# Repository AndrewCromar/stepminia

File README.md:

# Stepminia

Desktop finger stepmania dance-pad.

Assebly instructions [here](ASSEMBLY.md).

## PCB

Made in Kicad. Find the production files in the pcb folder to have it manufacured (JLCPCB).

You may notice the simple and integrated pcbs. This is because I wanted to learn how to integrate a microcontroller (rp2040) into my pcb design.. but when I went to have it made it was gonna cost $100! Its not that much but I have other things I wanna buy right now. So I made the simple version that just has holes for a Waveshare Zero to be soldered on.

## Firmware

The firmware is in the firmware folder and there will likly be a compiled version of it also in that folder.

> Wow really I had no clue the firmware would be in that folder bro.

## CAD

Right now I'm making the cad stuff in OnShape so I dont have files for it. I'll download the stls and put them in the cad folder when I'm done with them.

> I also my link to the OnShape files and/or download the files as solidworks parts if I can so people can make changes.

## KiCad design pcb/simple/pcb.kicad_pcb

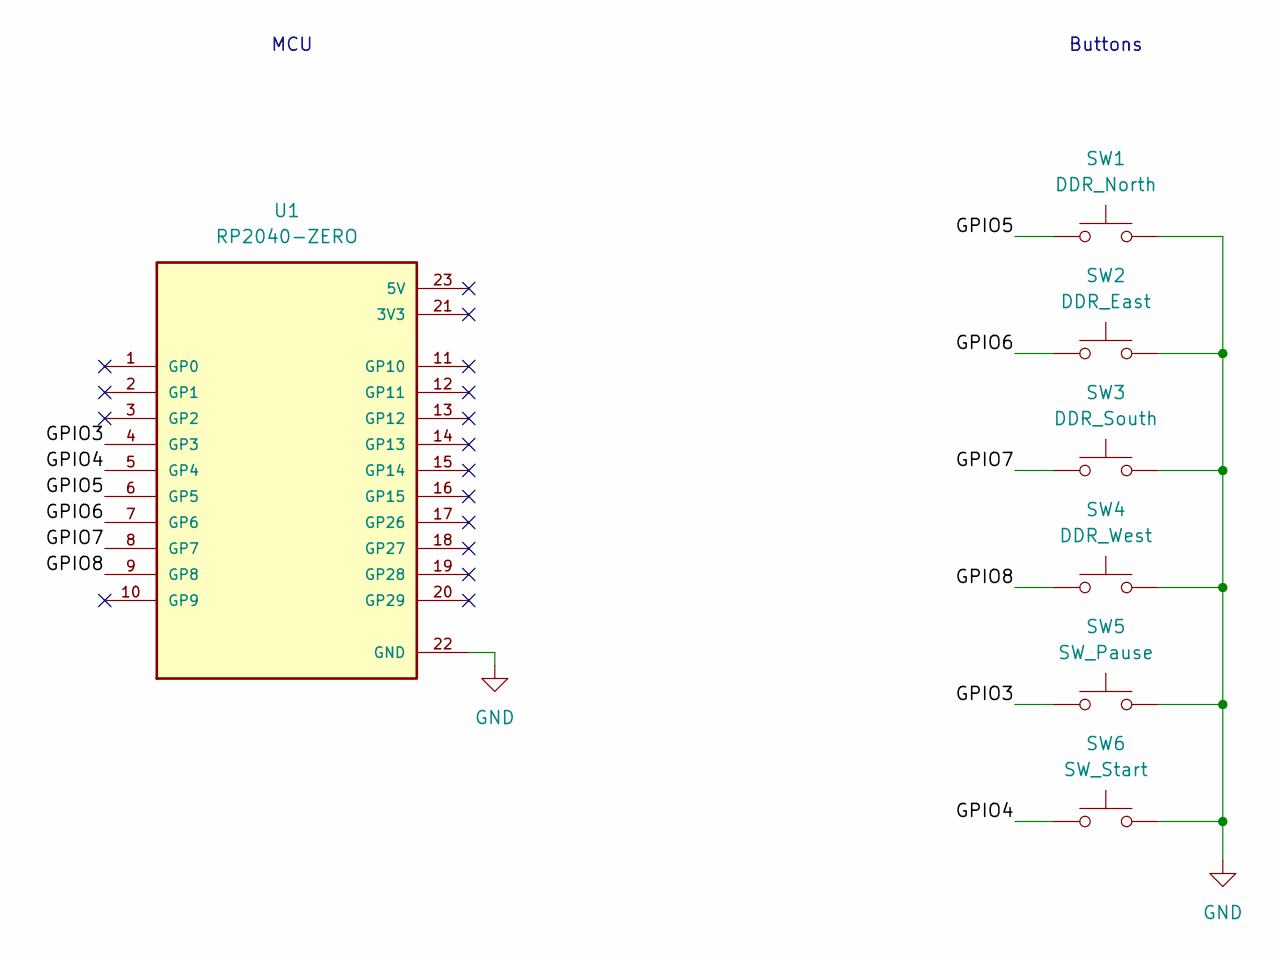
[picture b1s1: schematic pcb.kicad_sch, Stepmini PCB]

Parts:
SW1: DDR_North; DDR_CONTACT
SW2: DDR_East; DDR_CONTACT
SW3: DDR_South; DDR_CONTACT_MIRROR
SW4: DDR_West; DDR_CONTACT_MIRROR
SW5: SW_Pause; SW_PUSH_6mm
SW6: SW_Start; SW_PUSH_6mm
U1: RP2040-ZERO; MODULE_RP2040-ZERO; PARTREV NA

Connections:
/GPIO3: SW5.1, U1.4 (GP3)
/GPIO4: SW6.1, U1.5 (GP4)
/GPIO5: SW1.1, U1.6 (GP5)
/GPIO6: SW2.1, U1.7 (GP6)
/GPIO7: SW3.1, U1.8 (GP7)
/GPIO8: SW4.1, U1.9 (GP8)
GND: SW1.2, SW2.2, SW3.2, SW4.2, SW5.2, SW6.2, U1.22 (GND)

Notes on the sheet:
MCU
Buttons

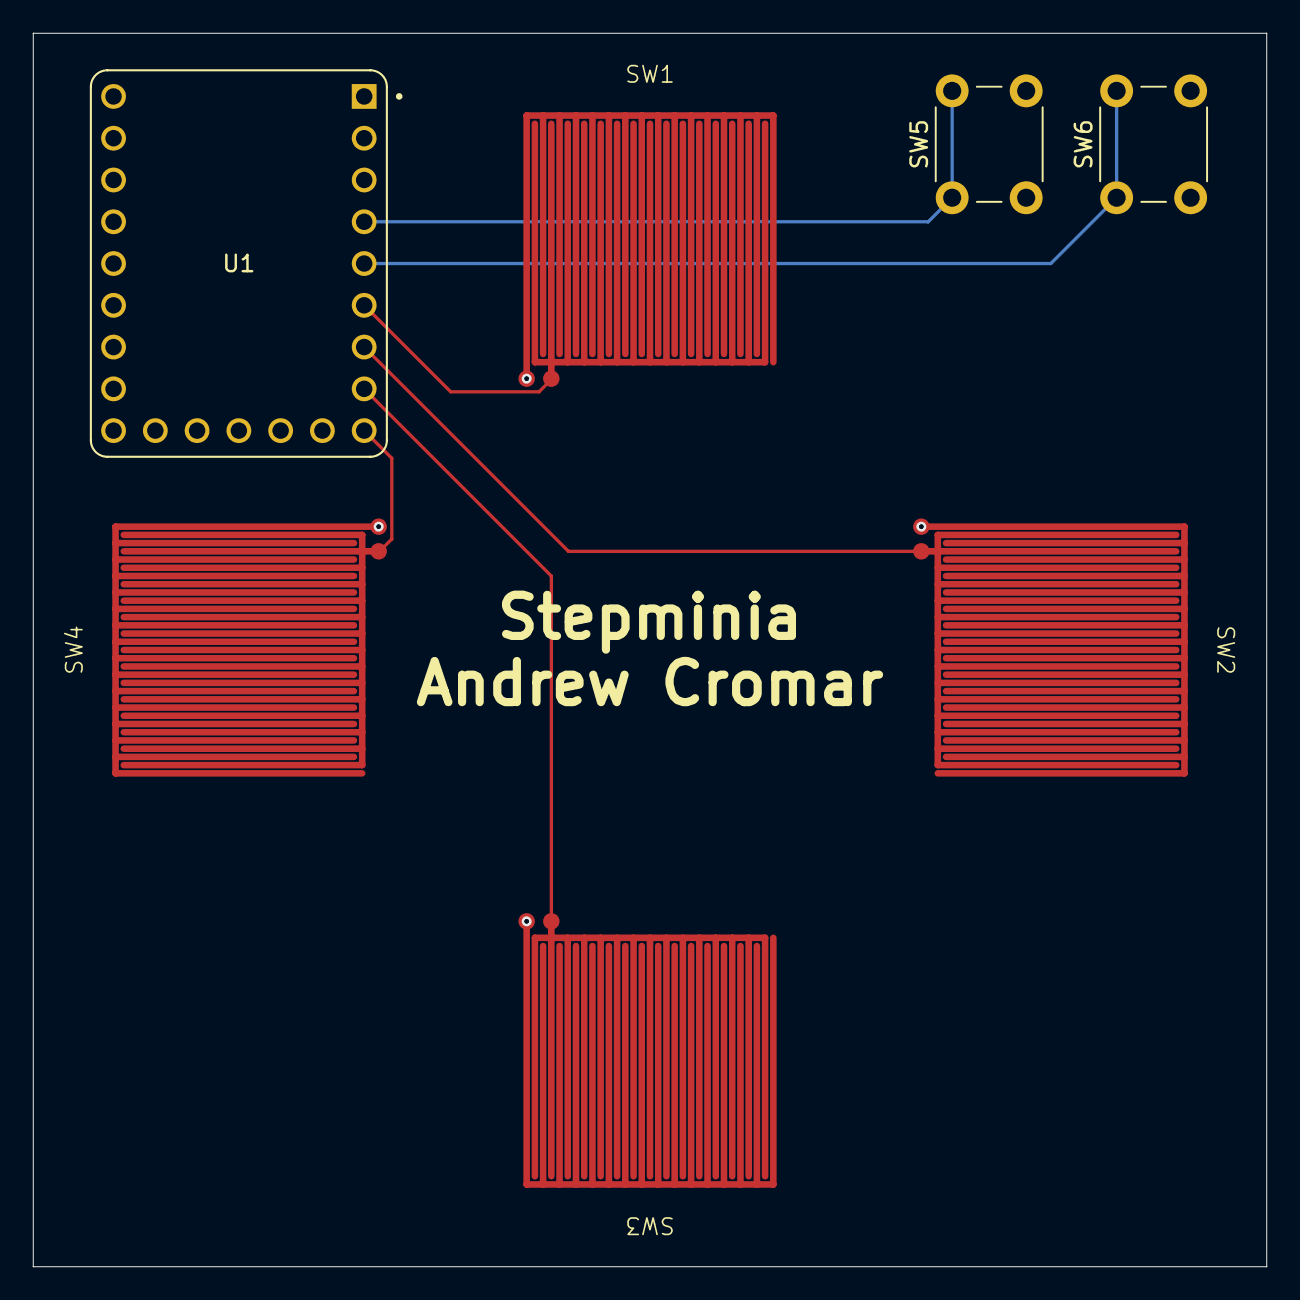
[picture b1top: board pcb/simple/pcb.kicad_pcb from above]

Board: 2 copper layers, 75.0 x 75.0 mm, 7 parts (0 on the bottom side), 7 nets.

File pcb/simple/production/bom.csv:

Designator,Footprint,Quantity,Value,LCSC Part #
SW1,DDR_CONTACT,1,DDR_North,
SW2,DDR_CONTACT,1,DDR_East,
SW3,DDR_CONTACT_MIRROR,1,DDR_South,
SW4,DDR_CONTACT_MIRROR,1,DDR_West,
SW5,SW_PUSH_6mm,1,SW_Pause,
SW6,SW_PUSH_6mm,1,SW_Start,
U1,MODULE_RP2040-ZERO,1,RP2040-ZERO,

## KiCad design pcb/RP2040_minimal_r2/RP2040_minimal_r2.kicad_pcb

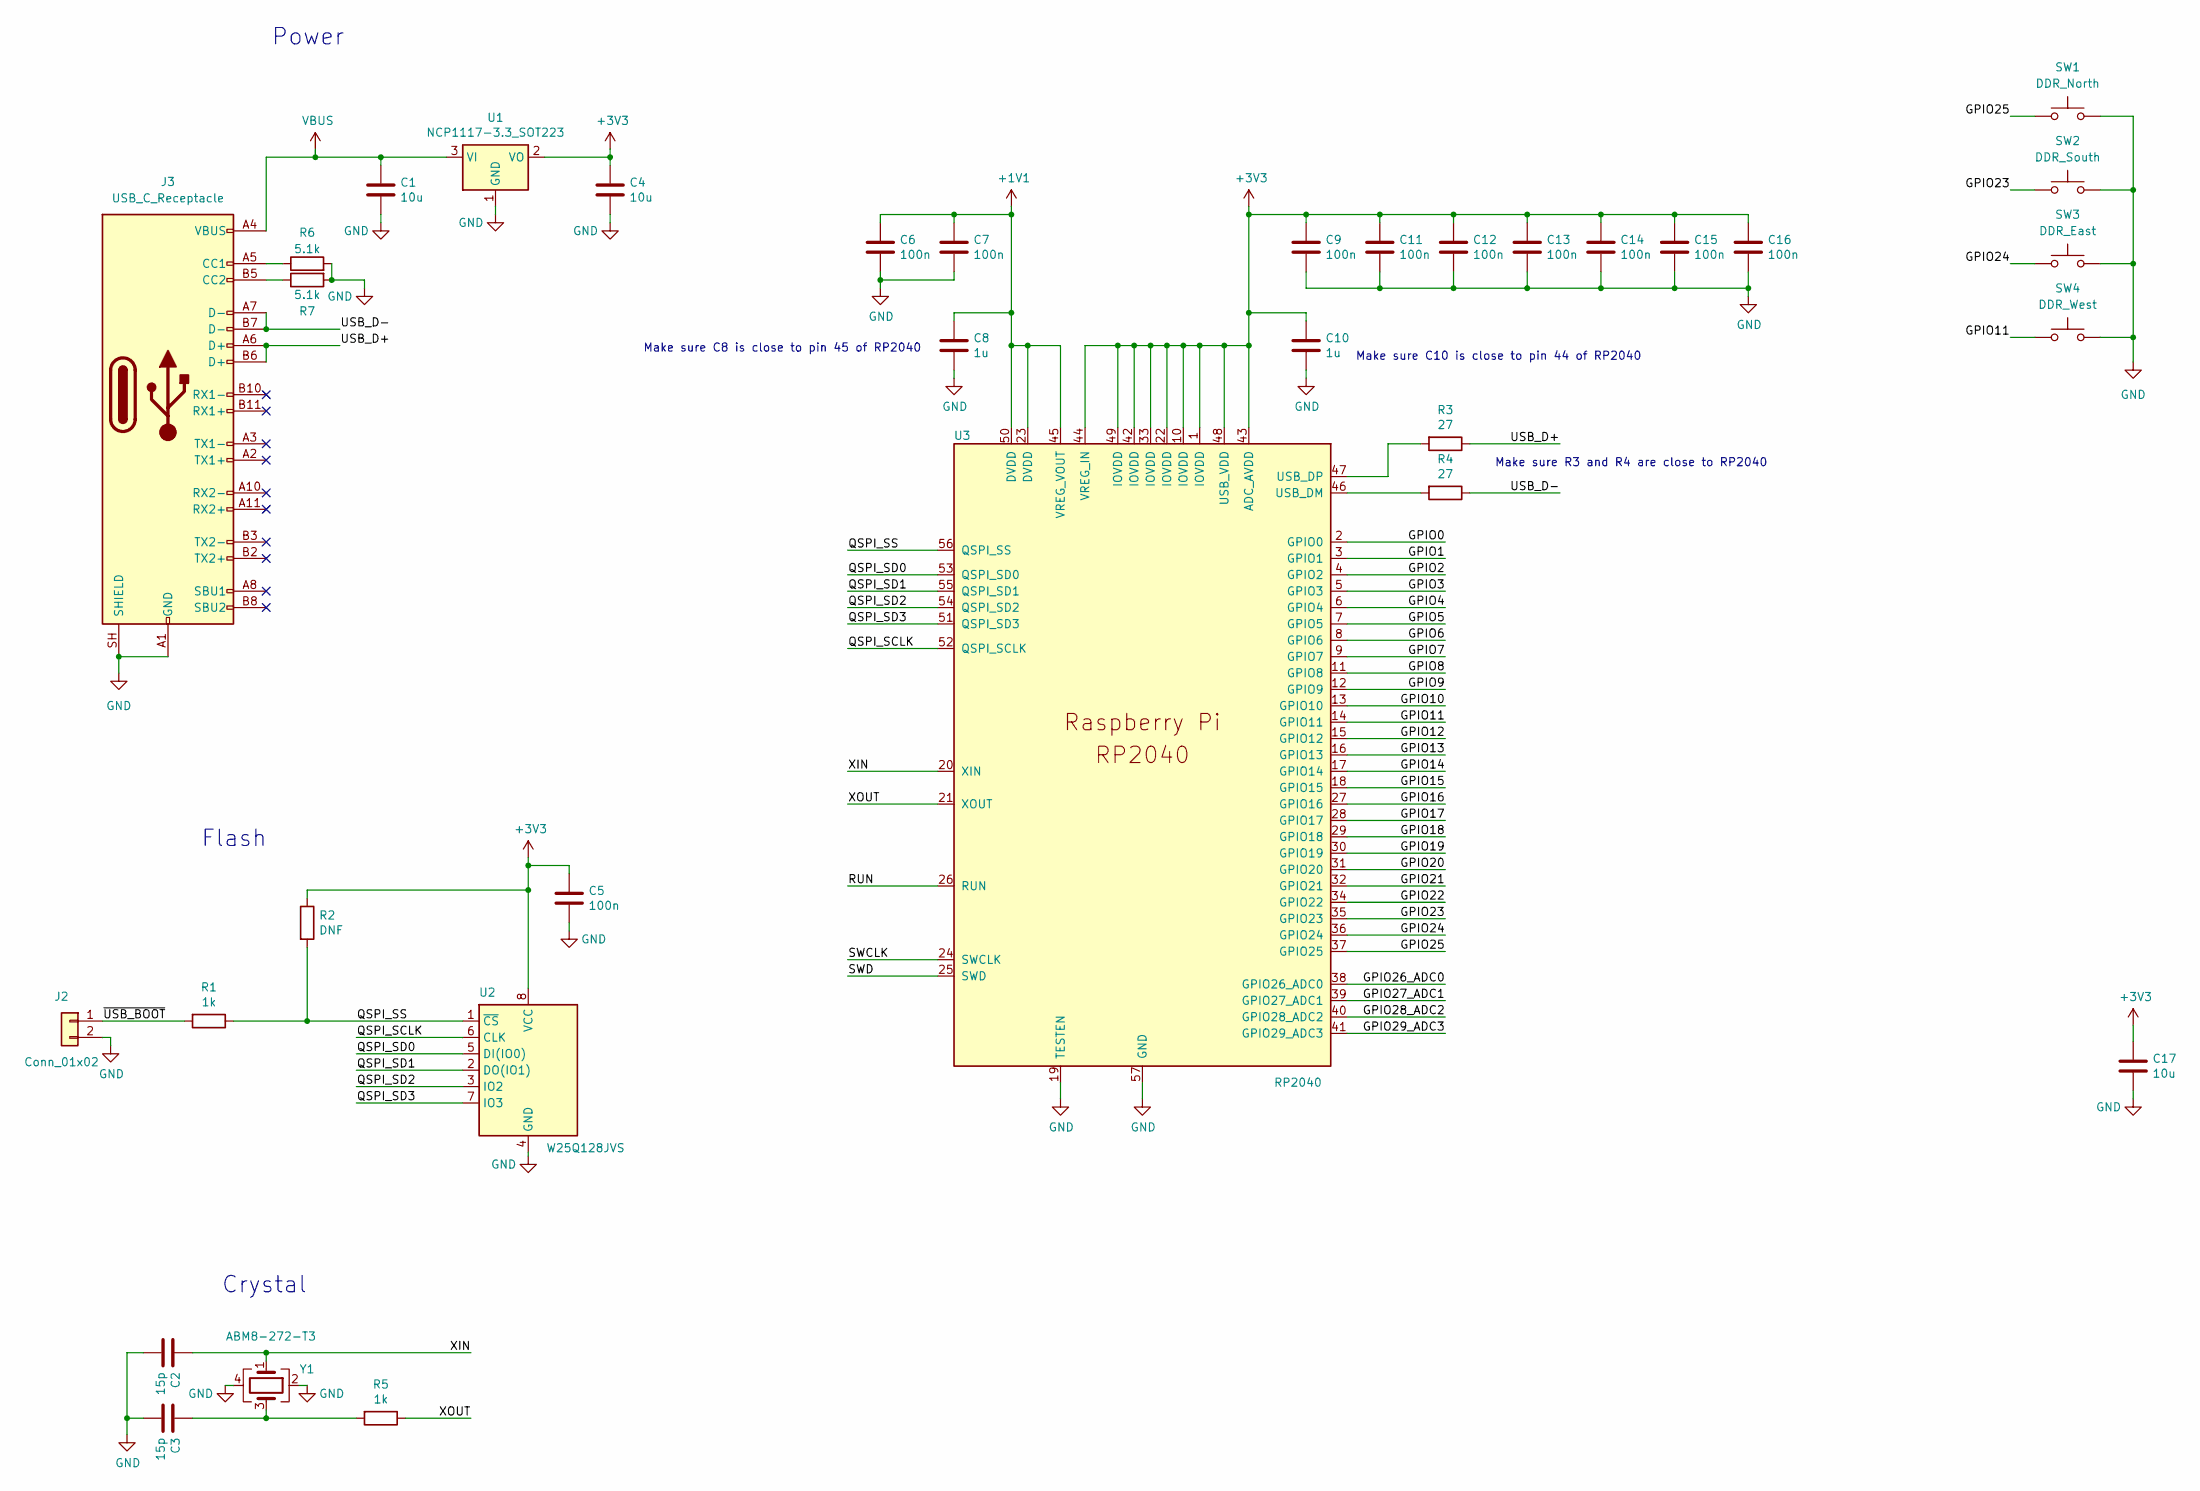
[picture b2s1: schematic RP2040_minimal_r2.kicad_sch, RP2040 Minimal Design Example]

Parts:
C1, C4, C17: 10u; C_0805_2012Metric
C2, C3: 15p; C_0402_1005Metric
C5, C6, C7, C9, C11, C12, C13, C14, C15, C16: 100n; C_0402_1005Metric
C8, C10: 1u; C_0402_1005Metric
J2: Conn_01x02; PinHeader_1x02_P2.54mm_Vertical
J3: USB_C_Receptacle; USB_C_Receptacle_GCT_USB4105-xx-A_16P_TopMnt_Horizontal
R1, R5: 1k; R_0402_1005Metric
R2: DNF; R_0402_1005Metric
R3, R4: 27; R_0402_1005Metric
R6, R7: 5.1k; R_0402_1005Metric
SW1: DDR_North; DDR_CONTACT_MIRROR
SW2: DDR_South; DDR_CONTACT
SW3: DDR_East; DDR_CONTACT
SW4: DDR_West; DDR_CONTACT
U1: NCP1117-3.3_SOT223; SOT-223-3_TabPin2
U2: W25Q128JVS; SOIC-8_5.23x5.23mm_P1.27mm
U3: RP2040; RP2040-QFN-56
Y1: ABM8-272-T3; Crystal_SMD_3225-4Pin_3.2x2.5mm

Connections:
+1V1: C6.1, C7.1, C8.1, U3.23 (DVDD), U3.45 (VREG_VOUT), U3.50 (DVDD)
+3V3: C4.1, C5.1, C9.1, C10.1, C11.1, C12.1, C13.1, C14.1, C15.1, C16.1, C17.1, R2.1, U1.2 (VO), U2.8 (VCC), U3.1 (IOVDD), U3.10 (IOVDD), U3.22 (IOVDD), U3.33 (IOVDD), U3.42 (IOVDD), U3.43 (ADC_AVDD), U3.44 (VREG_IN), U3.48 (USB_VDD), U3.49 (IOVDD)
/GPIO0: U3.2 (GPIO0)
/GPIO1: U3.3 (GPIO1)
/GPIO2: U3.4 (GPIO2)
/GPIO3: U3.5 (GPIO3)
/GPIO4: U3.6 (GPIO4)
/GPIO5: U3.7 (GPIO5)
/GPIO6: U3.8 (GPIO6)
/GPIO7: U3.9 (GPIO7)
/GPIO8: U3.11 (GPIO8)
/GPIO9: U3.12 (GPIO9)
/GPIO10: U3.13 (GPIO10)
/GPIO11: SW4.1, U3.14 (GPIO11)
/GPIO12: U3.15 (GPIO12)
/GPIO13: U3.16 (GPIO13)
/GPIO14: U3.17 (GPIO14)
/GPIO15: U3.18 (GPIO15)
/GPIO16: U3.27 (GPIO16)
/GPIO17: U3.28 (GPIO17)
/GPIO18: U3.29 (GPIO18)
/GPIO19: U3.30 (GPIO19)
/GPIO20: U3.31 (GPIO20)
/GPIO21: U3.32 (GPIO21)
/GPIO22: U3.34 (GPIO22)
/GPIO23: SW2.1, U3.35 (GPIO23)
/GPIO24: SW3.1, U3.36 (GPIO24)
/GPIO25: SW1.1, U3.37 (GPIO25)
/GPIO26_ADC0: U3.38 (GPIO26_ADC0)
/GPIO27_ADC1: U3.39 (GPIO27_ADC1)
/GPIO28_ADC2: U3.40 (GPIO28_ADC2)
/GPIO29_ADC3: U3.41 (GPIO29_ADC3)
/QSPI_SCLK: U2.6 (CLK), U3.52 (QSPI_SCLK)
/QSPI_SD0: U2.5 (DI(IO0)), U3.53 (QSPI_SD0)
/QSPI_SD1: U2.2 (DO(IO1)), U3.55 (QSPI_SD1)
/QSPI_SD2: U2.3 (IO2), U3.54 (QSPI_SD2)
/QSPI_SD3: U2.7 (IO3), U3.51 (QSPI_SD3)
/QSPI_SS: R1.1, R2.2, U2.1 (~CS), U3.56 (QSPI_SS)
/RUN: U3.26 (RUN)
/SWCLK: U3.24 (SWCLK)
/SWD: U3.25 (SWD)
/USB_D+: J3.A6 (D+), J3.B6 (D+), R3.1
/USB_D-: J3.A7 (D-), J3.B7 (D-), R4.1
/XIN: C2.1, U3.20 (XIN), Y1.1
/XOUT: R5.1, U3.21 (XOUT)
/~USB_BOOT: J2.1, R1.2
GND: C1.2, C2.2, C3.2, C4.2, C5.2, C6.2, C7.2, C8.2, C9.2, C10.2, C11.2, C12.2, C13.2, C14.2, C15.2, C16.2, C17.2, J2.2, J3.A1 (GND), J3.A12 (GND), J3.B1 (GND), J3.B12 (GND), J3.SH (SHIELD), R6.2, R7.2, SW1.2, SW2.2, SW3.2, SW4.2, U1.1 (GND), U2.4 (GND), U3.19 (TESTEN), U3.57 (GND), Y1.2, Y1.4
unnamed: C3.1, R5.2, Y1.3
unnamed: J3.A5 (CC1), R6.1
unnamed: J3.B5 (CC2), R7.1
unnamed: R4.2, U3.46 (USB_DM)
unnamed: R3.2, U3.47 (USB_DP)
VBUS: C1.1, J3.A4 (VBUS), J3.A9 (VBUS), J3.B4 (VBUS), J3.B9 (VBUS), U1.3 (VI)

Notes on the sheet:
Power
Crystal
Make sure C8 is close to pin 45 of RP2040
Make sure C10 is close to pin 44 of RP2040
Make sure R3 and R4 are close to RP2040
Flash

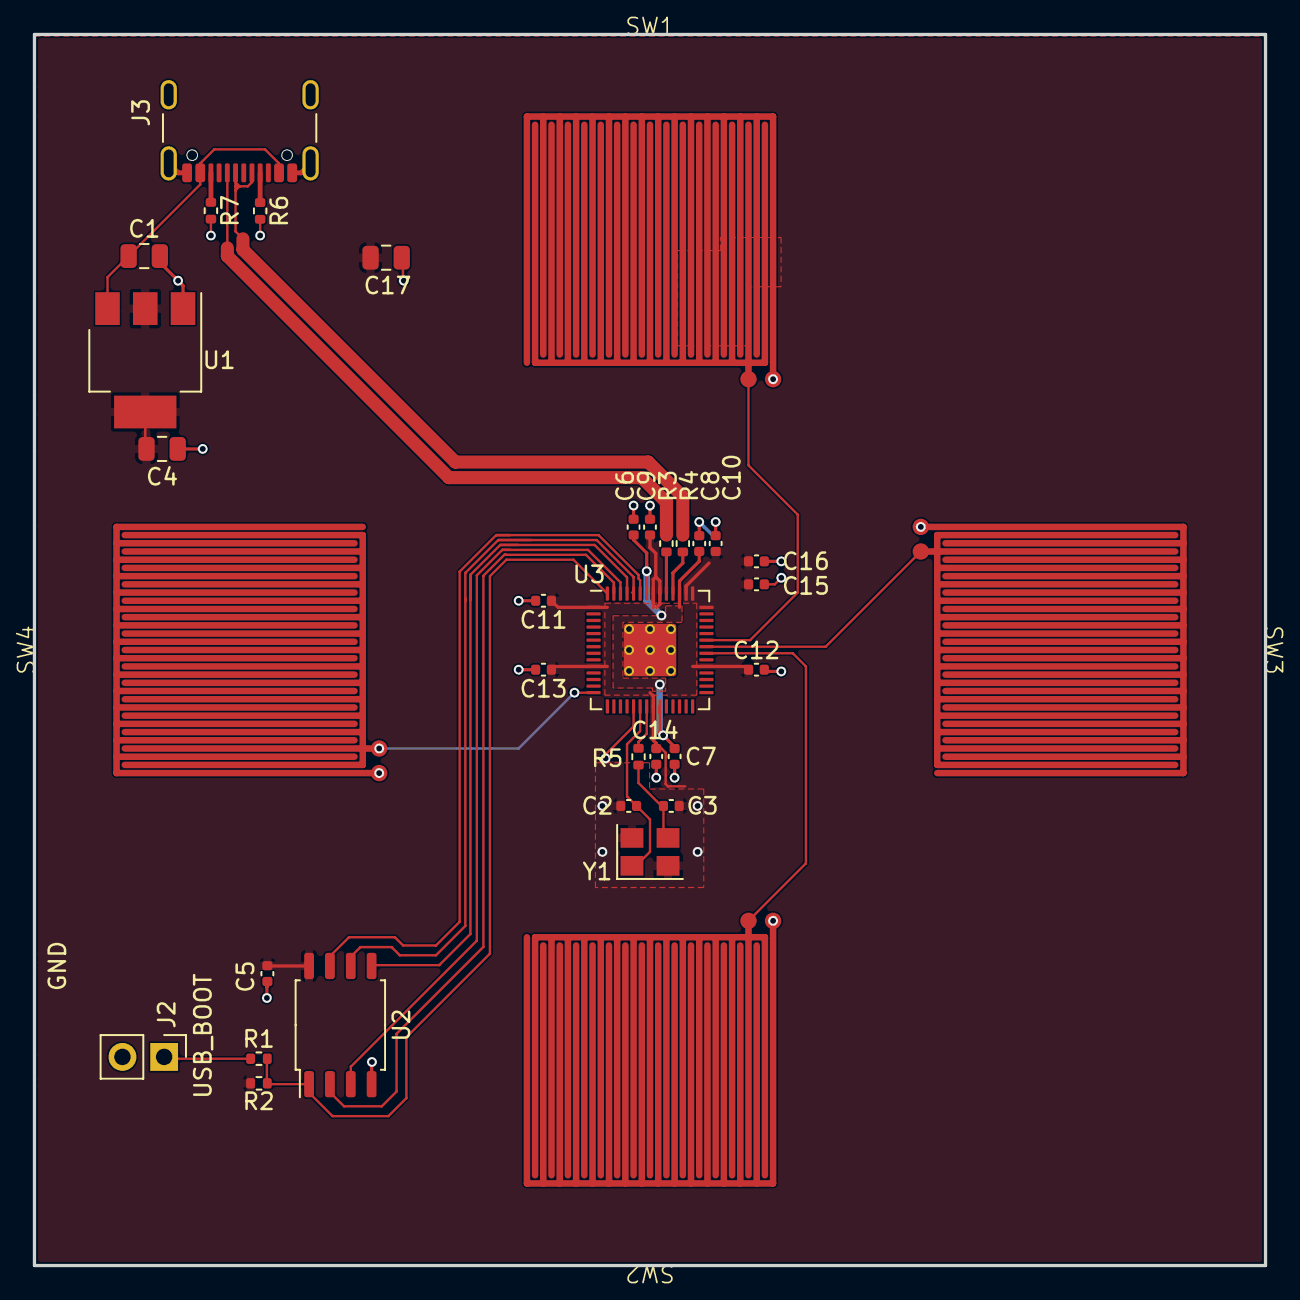
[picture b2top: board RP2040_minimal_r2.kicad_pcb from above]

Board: 2 copper layers, 75.0 x 75.0 mm, 34 parts (0 on the bottom side), 24 nets.

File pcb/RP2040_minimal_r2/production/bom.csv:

Designator,Footprint,Quantity,Value,LCSC Part #
"C1, C17, C4",0805,3,10u,C440198
"C10, C8",0402,2,1u,C29266
"C11, C12, C13, C14, C15, C16, C5, C6, C7, C9",0402,10,100n,C60474
"C2, C3",0402,2,15p,C86285
J2,PinHeader_1x02_P2.54mm_Vertical,1,Conn_01x02,
J3,USB_C_Receptacle_GCT_USB4105-xx-A_16P_TopMnt_Horizontal,1,USB_C_Receptacle,C2765186
"R1, R5",0402,2,1k,C106235
R2,0402,1,10k,C60490
"R3, R4",0402,2,27,C138021
"R6, R7",0402,2,5.1k,C105872
SW1,DDR_CONTACT_MIRROR,1,DDR_North,
SW2,DDR_CONTACT,1,DDR_South,
SW3,DDR_CONTACT,1,DDR_East,
SW4,DDR_CONTACT,1,DDR_West,
U1,SOT-223-3_TabPin2,1,NCP1117-3.3_SOT223,C26537
U2,SOIC-8_5.23x5.23mm_P1.27mm,1,W25Q128JVS,C113767
U3,RP2040-QFN-56,1,RP2040,C2040
Y1,Crystal_SMD_3225-4Pin_3.2x2.5mm,1,ABM8-272-T3,C20625731

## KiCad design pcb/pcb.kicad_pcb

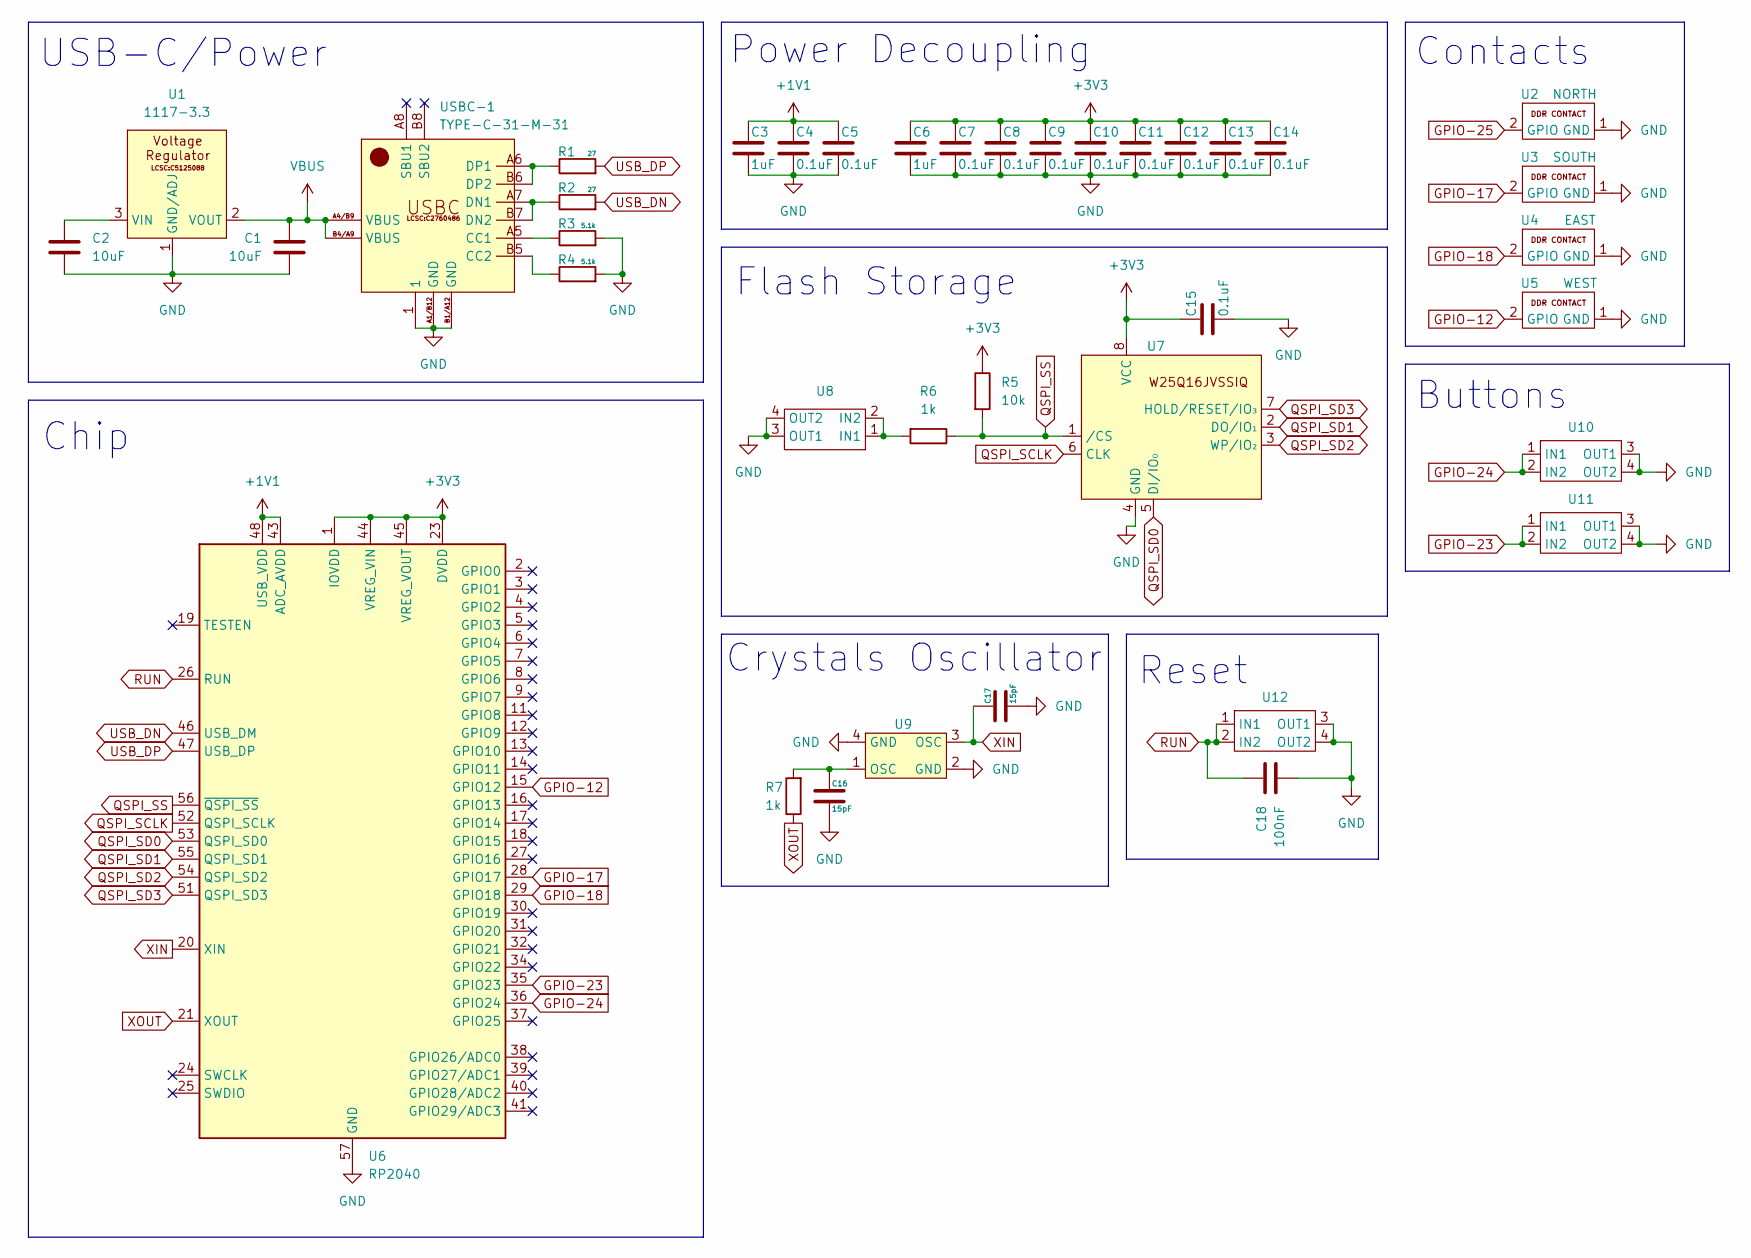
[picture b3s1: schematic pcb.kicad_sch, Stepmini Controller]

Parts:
C1, C2: 10uF; C_0201_0603Metric; LCSC C1691
C3, C6: 1uF; C_0201_0603Metric; LCSC C29936
C4, C5, C7, C8, C9, C10, C11, C12, C13, C14, C15: 0.1uF; C_0201_0603Metric; LCSC C1591
C16, C17: 15pF; C_0201_0603Metric; LCSC C1644
C18: 100nF; C_0201_0603Metric; LCSC C14663
R1, R2: 27; R_0201_0603Metric; LCSC C2907021
R3, R4: 5.1k; R_0201_0603Metric; LCSC C2907044
R5: 10k; R_0201_0603Metric; LCSC C98220
R6, R7: 1k; R_0201_0603Metric; LCSC C22548
U1: 1117-3.3; LCSC_SMD_1117-3.3v_C5125088; LCSC C5125088
U2: NORTH; DDR_CONTACT_MIRROR
U3: SOUTH; DDR_CONTACT
U4: EAST; DDR_CONTACT_MIRROR
U5: WEST; DDR_CONTACT
U6: RP2040; QFN-56-1EP_7x7mm_P0.4mm_EP3.2x3.2mm; LCSC RP2040
U7: LCSC_W25Q16JVSSIQ_C131025; LCSC C131025
U8, U10, U11, U12: LCSC_TS-1089S-02526_C455282; LCSC C455282
U9: LCSC_X322512MSB4SI_C9002; LCSC C9002
USBC-1: TYPE-C-31-M-31; LCSC_SMD_USBC_C2760486; LCSC C2760486

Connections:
+1V1: C3.1, C4.1, C5.1, U6.43 (ADC_AVDD), U6.48 (USB_VDD)
+3V3: C6.1, C7.1, C8.1, C9.1, C10.1, C11.1, C12.1, C13.1, C14.1, C15.1, R5.1, U6.1 (IOVDD), U6.10 (IOVDD), U6.22 (IOVDD), U6.23 (DVDD), U6.33 (IOVDD), U6.42 (IOVDD), U6.44 (VREG_VIN), U6.45 (VREG_VOUT), U6.49 (IOVDD), U6.50 (DVDD), U7.8 (VCC)
GND: C1.1, C2.2, C3.2, C4.2, C5.2, C6.2, C7.2, C8.2, C9.2, C10.2, C11.2, C12.2, C13.2, C14.2, C15.2, C16.2, C17.2, C18.1, R3.2, R4.2, U1.1 (GND/ADJ), U2.1 (GND), U3.1 (GND), U4.1 (GND), U5.1 (GND), U6.57 (GND), U7.4 (GND), U8.3 (OUT1), U8.4 (OUT2), U9.2 (GND), U9.4 (GND), U10.3 (OUT1), U10.4 (OUT2), U11.3 (OUT1), U11.4 (OUT2), U12.3 (OUT1), U12.4 (OUT2), USBC-1.1, USBC-1.A1/B12 (GND), USBC-1.B1/A12 (GND)
GPIO-12: U5.2 (GPIO), U6.15 (GPIO12)
GPIO-17: U3.2 (GPIO), U6.28 (GPIO17)
GPIO-18: U4.2 (GPIO), U6.29 (GPIO18)
GPIO-23: U6.35 (GPIO23), U11.1 (IN1), U11.2 (IN2)
GPIO-24: U6.36 (GPIO24), U10.1 (IN1), U10.2 (IN2)
GPIO-25: U2.2 (GPIO)
unnamed: C16.1, R7.2, U9.1 (OSC)
unnamed: C2.1, U1.3 (VIN)
unnamed: R6.2, U8.1 (IN1), U8.2 (IN2)
unnamed: R3.1, USBC-1.A5 (CC1)
unnamed: R4.1, USBC-1.B5 (CC2)
unnamed: R2.1, USBC-1.A7 (DN1), USBC-1.B7 (DN2)
unnamed: R1.1, USBC-1.A6 (DP1), USBC-1.B6 (DP2)
QSPI_SCLK: U6.52 (QSPI_SCLK), U7.6 (CLK)
QSPI_SD0: U6.53 (QSPI_SD0), U7.5 (DI/IO₀)
QSPI_SD1: U6.55 (QSPI_SD1), U7.2 (DO/IO₁)
QSPI_SD2: U6.54 (QSPI_SD2), U7.3 (WP/IO₂)
QSPI_SD3: U6.51 (QSPI_SD3), U7.7 (HOLD/RESET/IO₃)
QSPI_SS: R5.2, R6.1, U6.56 (~QSPI_SS), U7.1 (/CS)
RUN: C18.2, U6.26 (RUN), U12.1 (IN1), U12.2 (IN2)
USB_DN: R2.2, U6.46 (USB_DM)
USB_DP: R1.2, U6.47 (USB_DP)
VBUS: C1.2, U1.2 (VOUT), USBC-1.A4/B9 (VBUS), USBC-1.B4/A9 (VBUS)
XIN: C17.1, U6.20 (XIN), U9.3 (OSC)
XOUT: R7.1, U6.21 (XOUT)

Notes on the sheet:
Flash Storage
Power Decoupling
Crystals Oscillator
Contacts
USB-C/Power
Buttons
Reset
Chip

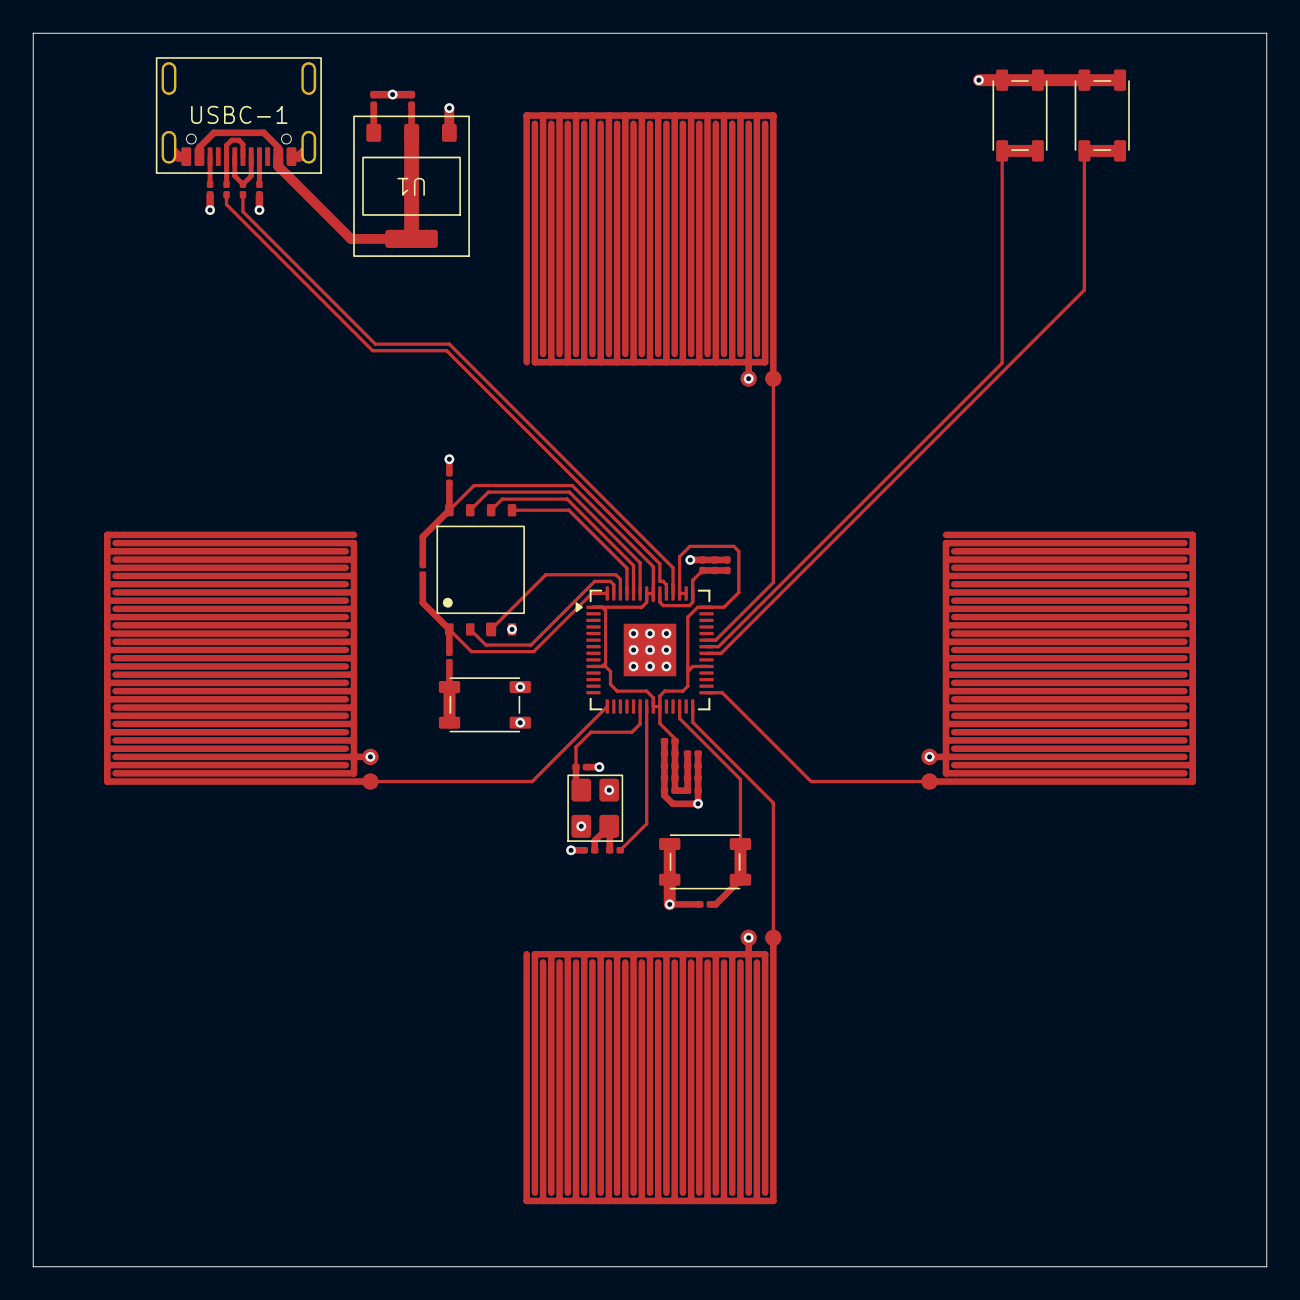
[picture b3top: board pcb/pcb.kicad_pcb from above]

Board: 2 copper layers, 75.0 x 75.0 mm, 38 parts (0 on the bottom side), 27 nets.

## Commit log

2026-04-13 more pcb work
2026-04-13 even more pcb work
2026-04-13 more pcb stuff yay
2026-04-13 started routing pcb
2026-04-13 saving things for the night
2026-04-13 one last things
2026-04-13 new version of the ddr pcb
2026-04-13 working on pcb even more
2026-04-13 temp files that got deleted
2026-04-14 there are problems :(
2026-04-15 make button lib
2026-04-15 work on it yay
2026-04-15 buttons on pcb
2026-04-15 more schematic work
    grounds are gay :(
2026-04-15 still working on it LOL
2026-04-16 working on usbc stuff
2026-04-16 usbc almost done
2026-04-16 started working on voltage regulator
2026-04-16 please
2026-04-16 start making footprint
2026-04-16 still working on it
2026-04-16 i think its all good
2026-04-16 added it to the pcb
2026-04-16 added footprints to c
2026-04-16 wired some stuff
2026-04-16 add vias and ground
2026-04-16 usbc schematic done?
2026-04-16 usb c stuff
2026-04-16 cleaned up old pcb_new and gitignore
2026-04-16 rename datasheets and add ams1117
2026-04-16 organize some files
2026-04-16 fixxed usbc stuff
2026-04-16 closing up for now
2026-04-20 work on schematic a bit
    - power decoupling
    - organize
2026-04-20 add stuff to pcb
2026-04-20 start work on ddr contact
2026-04-20 ddr footprint
2026-04-20 ddr contact sym
2026-04-20 working on ddr contacts n stuff
2026-04-20 still doing stuff
2026-04-20 Revert "still doing stuff"
    This reverts commit 534b6c4f653d7dddeed3be9c90f6de3e6d88290d.
2026-04-20 fixed ddr contacts
2026-04-20 make a mirrored version of ddr contact
2026-04-20 work on schematic more
2026-04-20 working on pcb
2026-04-21 working on new footprint
2026-04-21 same again
2026-04-21 make the symb now
    for W25Q16JVSSIQ
2026-04-21 working on schematic now
2026-04-21 button footprint
2026-04-21 work on schematic
2026-04-21 update pcb
2026-04-21 lots of pcb work
2026-04-21 more routing
2026-04-21 even more pcb stuff
2026-04-21 closing up
2026-04-24 make footprint
2026-04-24 fix footprint
2026-04-24 make symbol
2026-04-24 work on pcb
2026-04-24 work on pcb more
2026-05-13 clear v2
2026-05-13 add rp minimal example
2026-05-13 upt to newer kicad version
2026-05-13 add ddr contact
2026-05-13 add ddr contacts to pcb
2026-05-13 clean up pcb
2026-05-13 add gnd zone
2026-05-13 add usbc to schematic
2026-05-13 finish pcb i think
2026-05-13 move some stuff a bit
2026-05-13 start adding lcsc numbers
2026-05-13 add rest of lcsc numbers
2026-05-13 build prod files
2026-05-13 move some files
2026-05-13 finish pcb
2026-05-14 add readme
2026-05-26 starting work on firmware
2026-05-26 mostly working firmware
2026-05-26 firmware working
2026-05-26 build the uf2
2026-05-28 made graphics
2026-05-29 add images
2026-05-29 todo
2026-05-29 add cad files
2026-05-29 website stuff
2026-05-29 more website
2026-05-29 crop images
2026-05-29 few touch-ups
2026-05-29 few things - make guide page - move images to different folder
2026-05-29 favicon
2026-05-29 upt favicon
2026-06-02 start new site
2026-06-02 idk bout this
2026-06-02 vibecode up basic docs - to be worked on by human later ofc
2026-06-02 update some files
2026-06-02 reworking docs
2026-06-02 Fix Vercel build: drop redundant pip install
    Vercel auto-installs requirements.txt via uv; running pip install again
    hit externally-managed-environment (PEP 668). Just run mkdocs build.
2026-06-02 Use favicon as header logo
    Replaces the default material/library icon in the top-left with the
    project favicon.
2026-06-02 new logo
2026-06-02 fix logo
2026-06-02 oganize pcb files
2026-06-02 working on website
2026-06-02 zip some stuff
2026-06-02 working on guide
2026-06-02 finish up pcb page of the guide
2026-06-02 few changes to the site
2026-06-02 write firmware part of guide
2026-06-02 more website stuff
2026-06-02 add footer
